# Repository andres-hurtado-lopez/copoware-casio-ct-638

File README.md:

# copoware-casio-ct-638
MIDI interface for Casio CT-638 using RP-PICO 2040 board

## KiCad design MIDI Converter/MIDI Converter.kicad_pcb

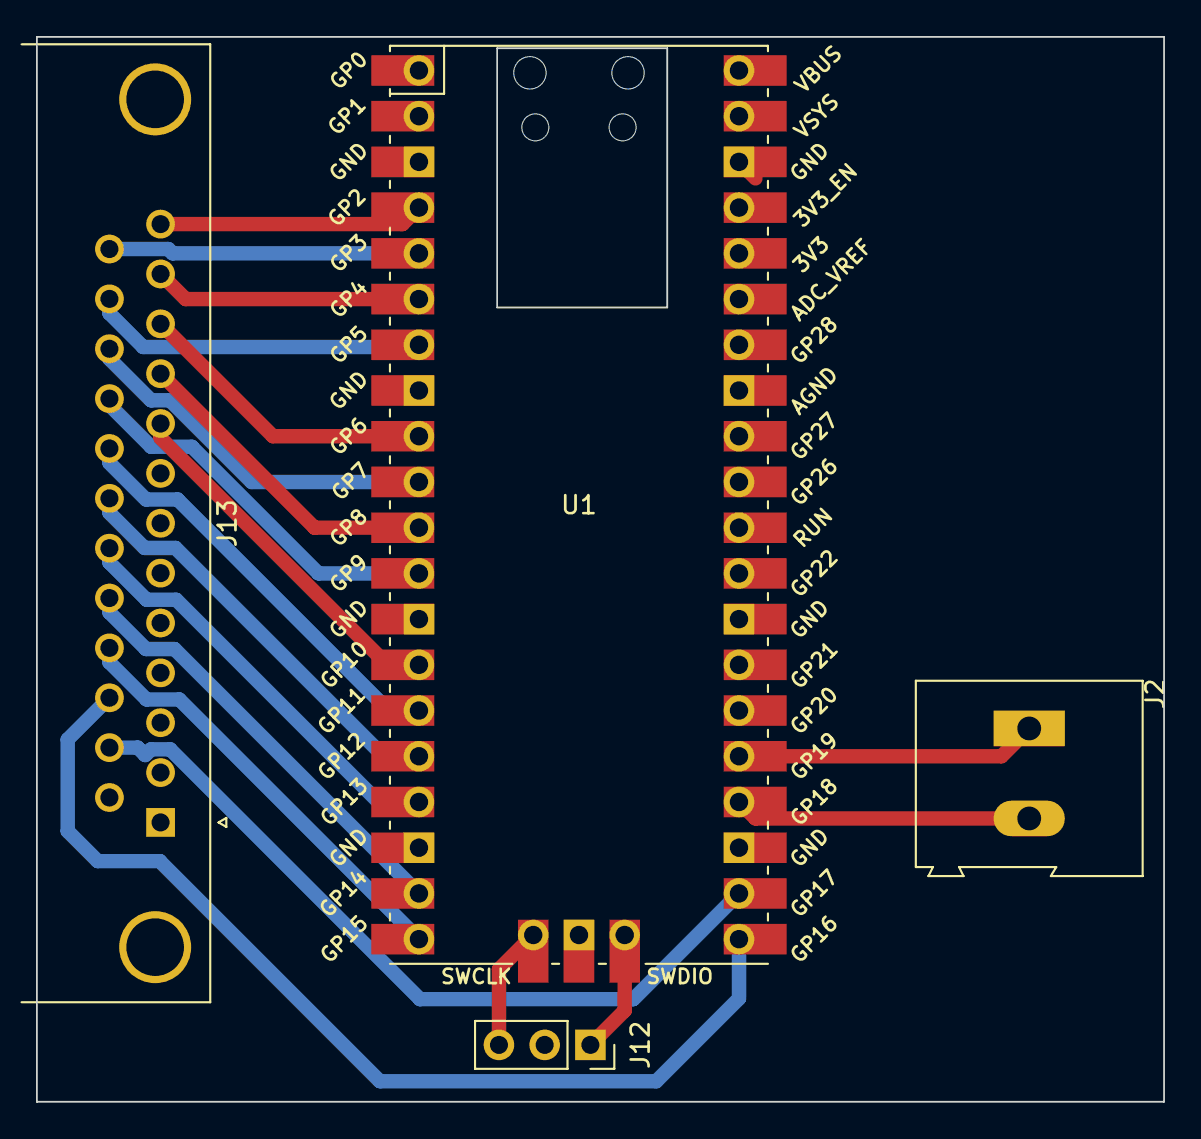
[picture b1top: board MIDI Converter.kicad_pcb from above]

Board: 2 copper layers, 62.6 x 59.2 mm, 4 parts (0 on the bottom side), 21 nets.

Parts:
J2: Screw_Terminal_01x02; TerminalBlock_Altech_AK300-2_P5.00mm
J12: Conn_01x03_Socket; PinSocket_1x03_P2.54mm_Vertical
J13: DB25_Plug_MountingHoles; DSUB-25_Female_Horizontal_P2.77x2.84mm_EdgePinOffset4.94mm_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
U1: Pico; RPi_Pico_SMD_TH

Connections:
GND: J12.2, J13.0 (PAD), U1.3 (GND), U1.8 (GND), U1.13 (GND), U1.18 (GND), U1.42 (GND)
unnamed: J2.1, U1.25 (GPIO19)
unnamed: J2.2, U1.24 (GPIO18)
unnamed: J12.1, U1.43 (SWDIO)
unnamed: J12.3, U1.41 (SWCLK)
unnamed: J13.15, U1.22 (GPIO17)
unnamed: J13.16, U1.21 (GPIO16)
unnamed: J13.17, U1.20 (GPIO15)
unnamed: J13.18, U1.19 (GPIO14)
unnamed: J13.19, U1.17 (GPIO13)
unnamed: J13.20, U1.16 (GPIO12)
unnamed: J13.21, U1.15 (GPIO11)
unnamed: J13.22, U1.12 (GPIO9)
unnamed: J13.23, U1.10 (GPIO7)
unnamed: J13.24, U1.7 (GPIO5)
unnamed: J13.25, U1.5 (GPIO3)
unnamed: J13.13, U1.4 (GPIO2)
unnamed: J13.12, U1.6 (GPIO4)
unnamed: J13.11, U1.9 (GPIO6)
unnamed: J13.10, U1.11 (GPIO8)
unnamed: J13.9, U1.14 (GPIO10)

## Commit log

2023-12-27 Version 0.1.0 Functional MIDI interface without speed control neither sustain pedal
2023-12-27 Picures, PCB design, CNC router layout
2024-01-07 Fixed socket size an refilled ground plane
2024-01-08 Final design sent to JLCPCB on 2024-01-07
